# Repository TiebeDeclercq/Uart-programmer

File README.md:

# Custom UART Programmer

A versatile UART programming board designed for microcontroller development with flexible voltage selection and multiple connection options. Features built-in status LEDs, CH340C USB-to-serial conversion, and support for external programming fixtures.

## **Hardware Overview**

- **USB-to-Serial IC:** CH340C for reliable USB communication
- **Voltage Selection:** Jumper-selectable 3.3V or 5V operation
- **Status Indicators:**
    - Power LED (PWR)
    - TX/RX activity LEDs
- **Connection Options:**
    - Standard pin headers for jumper wire connections
    - FCP slot for external fixtures
- **Interface:** Standard UART (TX, RX, VCC, GND, BOOT, EN)
- **Power Supply:** USB-powered with onboard voltage regulation

## **Schematic**

## **Getting Started**

1. **Driver Installation**
    
    - Install CH340 drivers for your operating system
    - Windows: Download from manufacturer or use Windows Update
    - macOS/Linux: Usually plug-and-play
2. **Voltage Selection**
    
    - Set jumper to 3.3V for ESP32, ESP8266, and other 3.3V microcontrollers
    - Set jumper to 5V for Arduino and 5V-compatible devices
3. **Connection Methods**
    
    **Method A: Direct Jumper Connections**
    
    - Connect VCC to target microcontroller's power pin
    - Connect GND to target ground
    - Connect TX to target RX pin
    - Connect RX to target TX pin
    - Use BOOT and EN pins for programming mode control (ESP32/ESP8266)
    
    **Method B: External Programming Fixture**
    
    - Insert compatible pogo pin module into FCP slot
    - Align fixture with target board
    - Programming connections are made automatically
4. **Programming**
    
    - Open your preferred serial terminal or IDE
    - Select the correct COM port
    - Set appropriate baud rate (typically 115200)
    - Put target microcontroller in programming mode
    - Upload firmware
5. **Status Monitoring**
    
    - PWR LED indicates power is applied
    - TX LED flashes during data transmission
    - RX LED flashes during data reception

**More Projects:** Visit [dectronics.cc](https://dectronics.cc/) for additional electronics projects

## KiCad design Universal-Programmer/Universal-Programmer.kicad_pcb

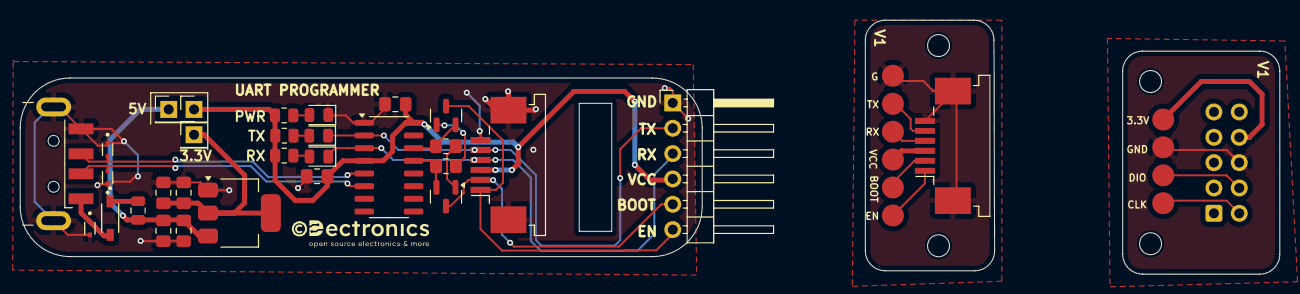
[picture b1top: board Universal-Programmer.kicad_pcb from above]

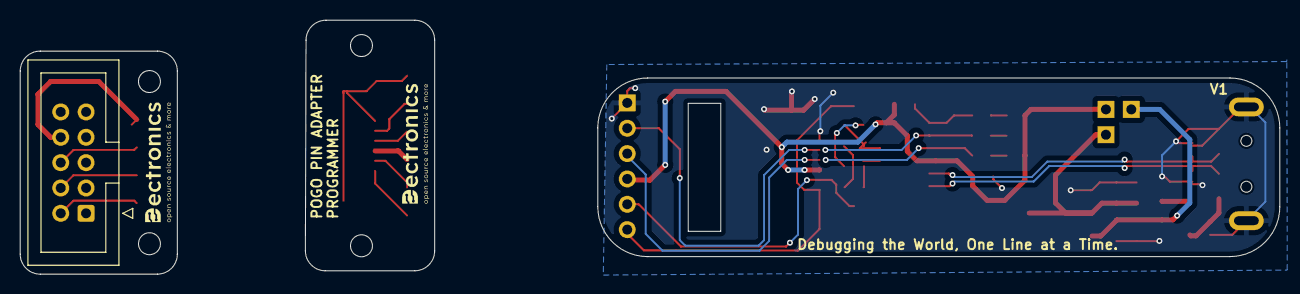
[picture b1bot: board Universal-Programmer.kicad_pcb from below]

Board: 2 copper layers, 126.2 x 25.5 mm, 43 parts (5 on the bottom side), 19 nets.

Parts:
C1, C2: 100nF; C_0805_2012Metric_Pad1.18x1.45mm_HandSolder
C3, C5: 10uF; C_0805_2012Metric_Pad1.18x1.45mm_HandSolder
C4, C6: 0.1uF; C_0805_2012Metric_Pad1.18x1.45mm_HandSolder
D1, D2, D3: LED; LED_0805_2012Metric
D4: 1N5819HW-7-F; SOD3715X145N
D5, D6, D7: LESD5D5.0CT1G; TVS_LESD5D5.0CT1G
F1: Fuse_Small; Fuse_0805_2012Metric
H1, H2, H3, H4: MountingHole; MountingHole_2.2mm_M2
J1: USB_A; USB_A_CNCTech_1001-011-01101_Horizontal
J2: Conn_01x06_Pin; PinHeader_1x06_P2.54mm_Horizontal
J3, J4: Conn_01x06_MountingPin; TE_84953-6_1x06-1MP_P1.0mm_Horizontal
J5, J6, J7, J8, J9, J10, J11, J12, J13, J14: Conn_01x01_Pin; HARWIN_P70-1000045R
J19: Conn_02x05_Odd_Even; IDC-Header_2x05_P2.54mm_Vertical
JP1: Jumper_3_Open; VoltageJumper
Q1, Q2: MMBT3904; SOT-23
R1, R2: 10kΩ; R_0805_2012Metric_Pad1.20x1.40mm_HandSolder
R3: 750; R_0805_2012Metric
R4, R5: 1k; R_0805_2012Metric
U1: CH340C; SOIC-16_3.9x9.9mm_P1.27mm
U2: AMS1117-3.3; SOT-223-3_TabPin2

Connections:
+3.3V: C3.1, C4.1, JP1.3 (B), U2.2 (VO)
+5V: C5.1, C6.1, F1.2, JP1.1 (A), U2.3 (VI)
/D_N: D6.2, J1.2 (D-), U1.6 (UD-)
/D_P: D5.2, J1.3 (D+), U1.5 (UD+)
BOOT: J2.5, J4.2, Q2.3 (C)
EN: J2.6, J4.1, Q1.3 (C)
GND: C1.1, C2.2, C3.2, C4.2, C5.2, C6.2, D1.1 (K), D5.1, D6.1, D7.2, J1.4 (GND), J1.5 (Shield), J2.1, J4.6, J4.MP (MountPin), U1.1 (GND), U2.1 (GND)
unnamed: D1.2 (A), R3.2
unnamed: D2.2 (A), R4.2
unnamed: D3.2 (A), R5.2
unnamed: D4.C, F1.1
unnamed: D4.A, D7.1, J1.1 (VBUS)
unnamed: Q1.1 (B), R1.2
unnamed: Q1.2 (E), R2.1, U1.14 (~RTS)
unnamed: Q2.1 (B), R2.2
unnamed: Q2.2 (E), R1.1, U1.13 (~DTR)
RX: D3.1 (K), J2.3, J4.4, U1.3 (RXD)
TX: D2.1 (K), J2.2, J4.5, U1.2 (TXD)
VCC: C1.2, C2.1, J2.4, J4.3, JP1.2 (C), R3.1, R4.1, R5.1, U1.4 (V3), U1.16 (VCC)

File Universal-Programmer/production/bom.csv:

Designator,Footprint,Quantity,Value,LCSC Part #
"C1, C2",0805,2,100nF,
"C3, C5",0805,2,10uF,
"C4, C6",0805,2,0.1uF,
"D1, D2, D3",0805,3,LED,
D4,SOD3715X145N,1,1N5819HW-7-F,
"D5, D6, D7",TVS_LESD5D5.0CT1G,3,LESD5D5.0CT1G,
F1,0805,1,Fuse_Small,
J1,USB_A_CNCTech_1001-011-01101_Horizontal,1,USB_A,
J2,PinHeader_1x06_P2.54mm_Horizontal,1,Conn_01x06_Pin,
J4,TE_84953-6_1x06-1MP_P1.0mm_Horizontal,1,Conn_01x06_MountingPin,
"Q1, Q2",SOT-23,2,MMBT3904,
"R1, R2",0805,2,10kΩ,
R3,0805,1,750,
"R4, R5",0805,2,1k,
U1,SOIC-16_3.9x9.9mm_P1.27mm,1,CH340C,
U2,SOT-223-3_TabPin2,1,AMS1117-3.3,

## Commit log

2025-06-17 INIT
2025-08-16 Images
